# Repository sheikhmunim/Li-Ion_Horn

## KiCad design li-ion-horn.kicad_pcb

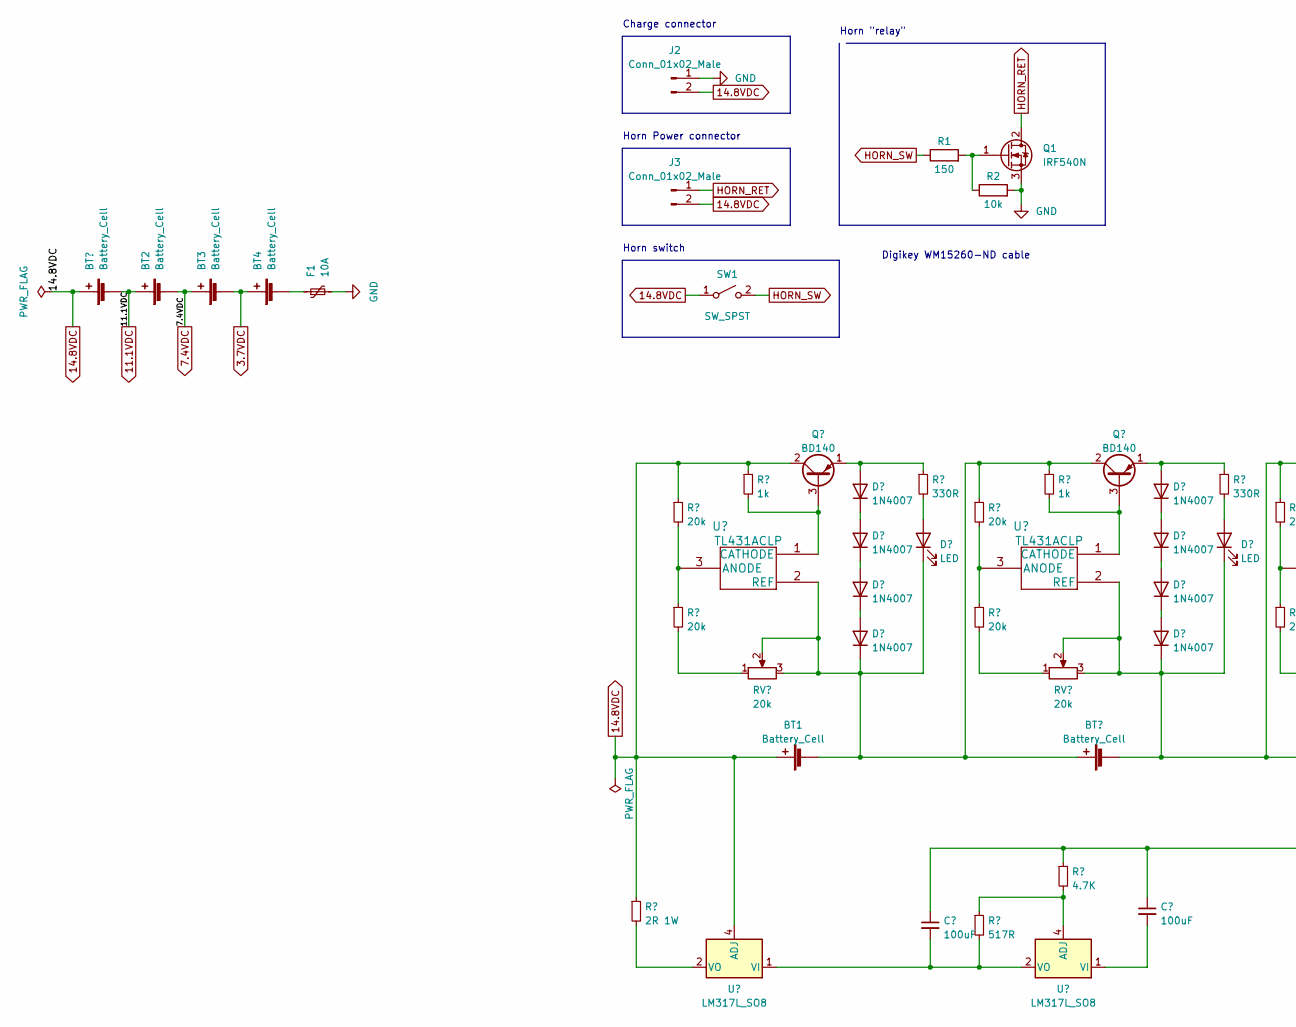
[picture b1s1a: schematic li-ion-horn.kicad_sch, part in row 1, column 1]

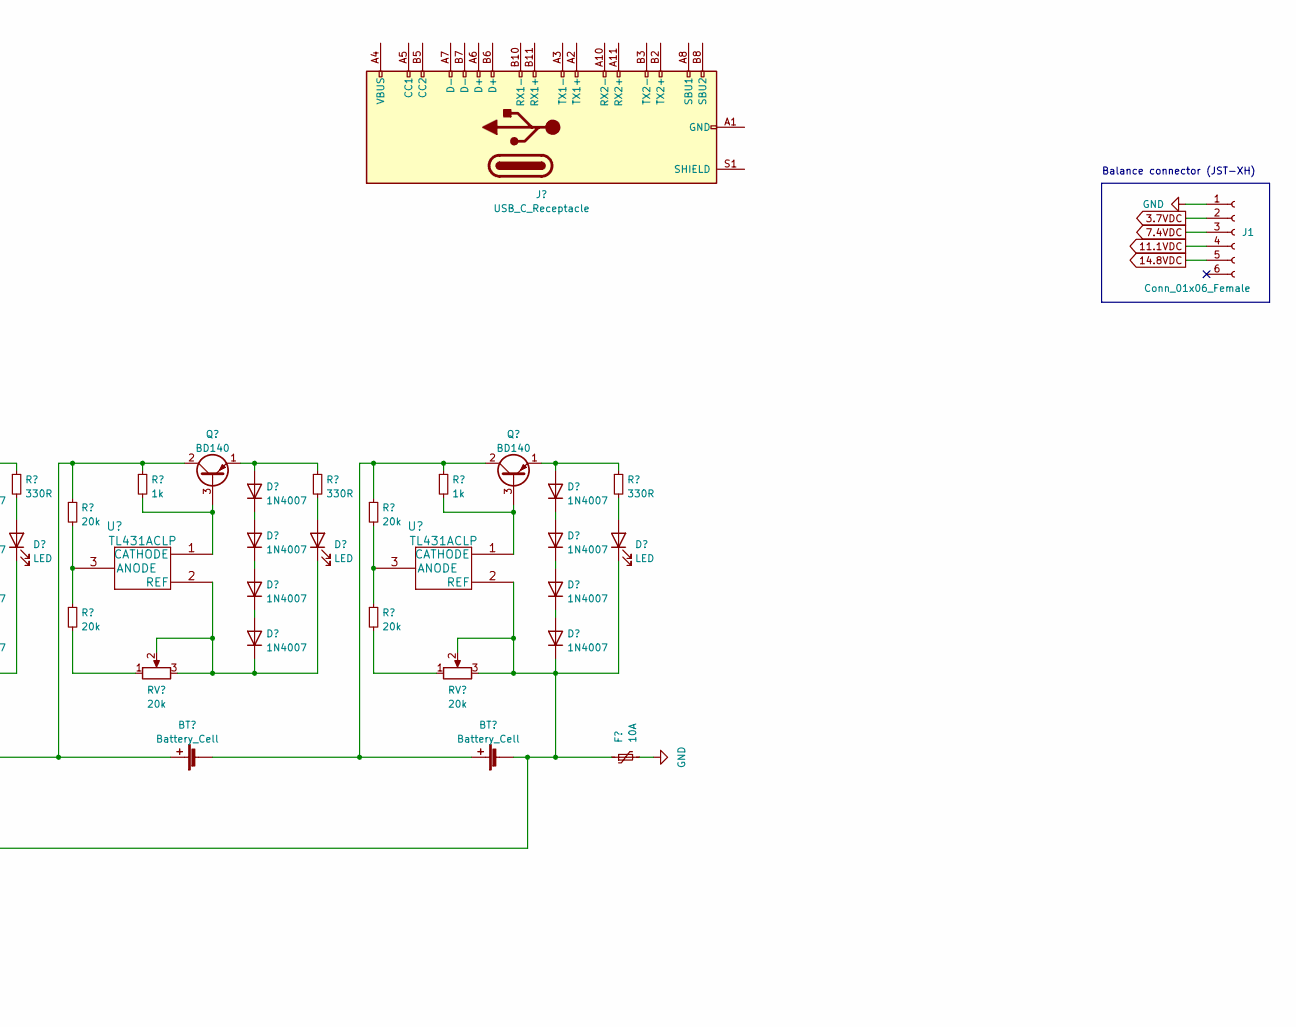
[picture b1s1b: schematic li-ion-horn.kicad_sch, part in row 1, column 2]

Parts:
BT1, BT2, BT3, BT4: Battery_Cell; BatteryHolder_Keystone_1042_1x18650
F1: 10A; Fuseholder_Blade_Mini_Keystone_3568
J1: Conn_01x06_Female; PinSocket_1x06_P2.54mm_Horizontal
J2: Conn_01x02_Male; AMASS_XT60PW-M
J3: Conn_01x02_Male; AMASS_XT60-F_1x02_P7.20mm_Vertical
Q1: IRF540N; TO-220-3_Horizontal_TabDown
R1: 150; R_Axial_DIN0204_L3.6mm_D1.6mm_P2.54mm_Vertical
R2: 10k; R_Axial_DIN0204_L3.6mm_D1.6mm_P2.54mm_Vertical
SW1: SW_SPST; PinHeader_1x02_P2.54mm_Vertical

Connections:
3.7VDC: BT3.2 (-), BT4.1 (+), J1.2
7.4VDC: BT2.2 (-), BT3.1 (+), J1.3
11.1VDC: BT1.2 (-), BT2.1 (+), J1.4
14.8VDC: BT1.1 (+), J1.5, J2.2, J3.2, SW1.1 (A)
GND: F1.2, J1.1, J2.1, Q1.3 (S), R2.2
HORN_RET: J3.1, Q1.2 (D)
HORN_SW: R1.1, SW1.2 (B)
unnamed: BT4.2 (-), F1.1
unnamed: Q1.1 (G), R1.2, R2.1

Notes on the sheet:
Horn switch
Horn Power connector
Balance connector (JST-XH)
Digikey WM15260-ND cable
Charge connector
Horn "relay"

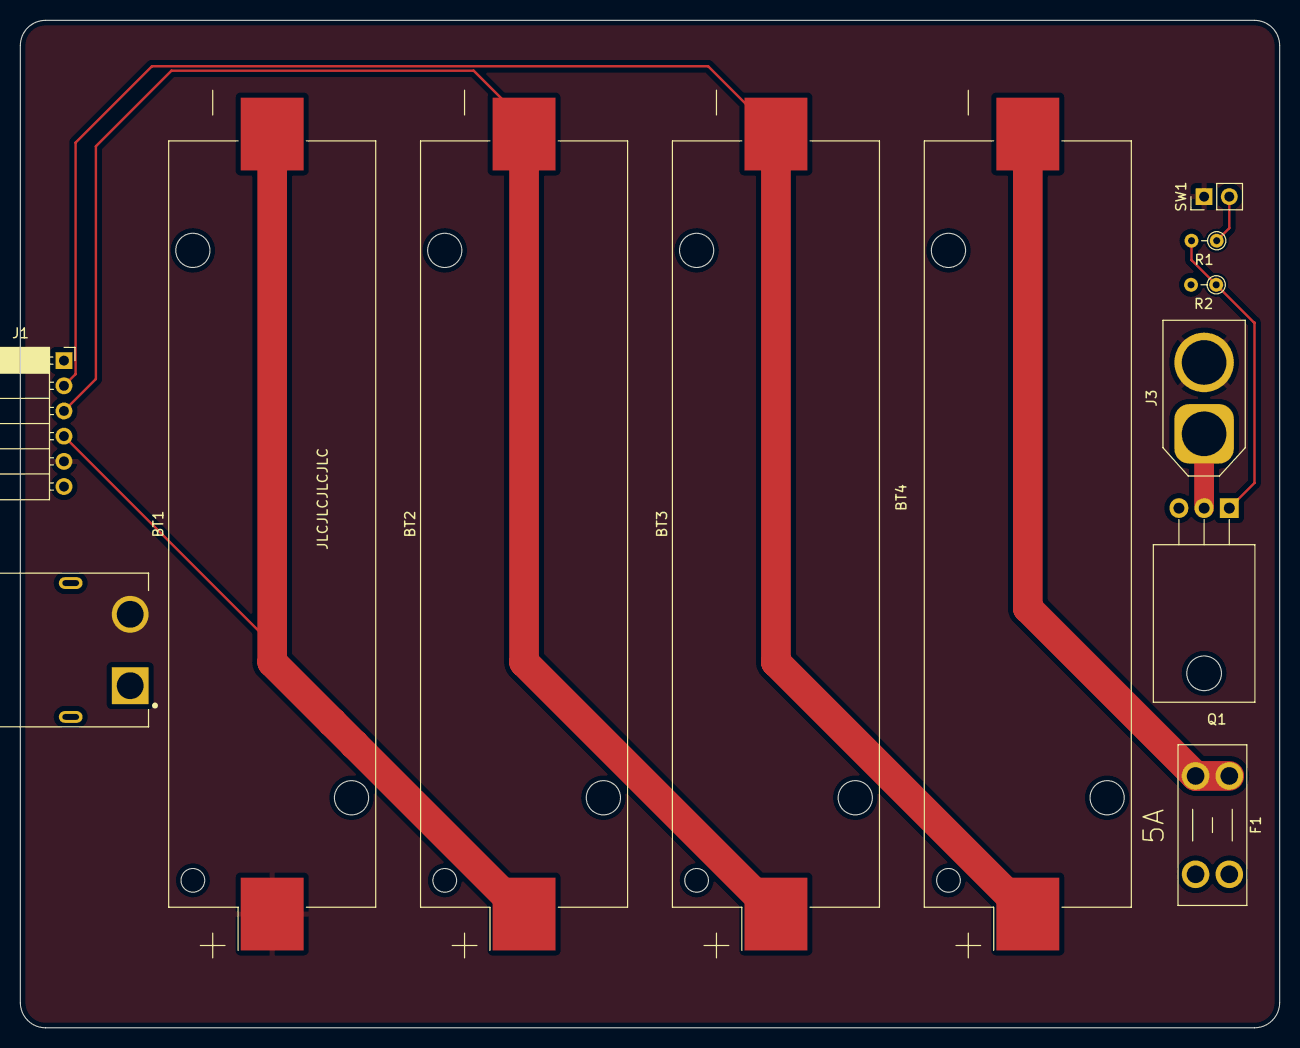
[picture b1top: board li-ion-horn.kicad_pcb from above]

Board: 2 copper layers, 127.0 x 101.6 mm, 12 parts (0 on the bottom side), 9 nets.
